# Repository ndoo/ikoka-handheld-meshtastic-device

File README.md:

# Ikoka Handheld Meshtastic Device

## Ikoka! (行こか!)

“行こか?” or “行こか!” is [Kansai dialect](https://en.wikipedia.org/wiki/Kansai_dialect) for “shall we go?” or “let’s go!”.

I hope that building these long-range Meshtastic designs inspires you to go on your next [DXing](https://en.wikipedia.org/wiki/DXing) adventure.

## Features

- LoRa
  - Up to 33 dBm (2 W) output power
  - 410–493 MHz (433 MHz band) or 850–930 MHz (868/915/923 MHz band)
- Bluetooth 5 LE
- Lithium-ion battery with charging
- 0.96" OLED display

Feature set above depends on part selection.

### Hardware

### Parts Selection

Several options are available depending on the feature set you need.

#### Microcontroller

- [Seeed Studio XIAO-nRF52840](https://www.seeedstudio.com/Seeed-XIAO-BLE-nRF52840-p-5201.html) - Bluetooth 5/LE

#### LoRa Module

- [E22-400M22S](https://www.cdebyte.com/products/E22-400M22S) (410–493 MHz at 22 dBm)
- [E22-400M30S](https://www.cdebyte.com/products/E22-400M30S) (410–493 MHz at 30 dBm)
- [E22-400M33S](https://www.cdebyte.com/products/E22-400M33S) (410–493 MHz at 33 dBm)
- [E22-900M22S](https://www.cdebyte.com/products/E22-900M22S) (850–930 MHz at 22 dBm)
- [E22-900M30S](https://www.cdebyte.com/products/E22-900M30S) (850–930 MHz at 30 dBm)
- [E22-900M33S](https://www.cdebyte.com/products/E22-900M33S) (850–930 MHz at 33 dBm)

#### Lithium-ion Battery (4.2V charging termination, optional)

- Lithium-polymer pouch battery cell (4.2V charge termination; connector: Molex PicoBlade 1x02P, pitch 1.25mm)

#### OLED Display (Optional)

- Generic SSD1306 0.96" OLED display modules with FPC connector ([Vishay OLED-128O064D-BPP3N00000](https://www.vishay.com/en/product/37902/) or generic OLEDs with the same connector dimensions and pinout)

## Firmware

### GPIO Assignment

| XIAO Pin | Function | XIAO-nRF52840 | XIAO-ESP32-S3 |
|---|---|---|---|
| 1 (D0) | User button | 2 (P0.02) | 1 |
| 2 (D1) | EBYTE E22 - DIO1 | 3 (P0.03) | 2 |
| 3 (D2) | EBYTE E22 - RST | 28 (P0.28) | 3 |
| 4 (D3) | EBYTE E22 - BUSY | 29 (P0.29) | 4 |
| 5 (D4) | EBYTE E22 - SPI NSS | 4 (P0.04) | 5 |
| 6 (D5) | EBYTE E22 - RXEN | 5 (P0.05) | 6 |
| 7 (D6) | SSD1306 OLED - I2C SDA | 43 (P1.11) | 43 |
| 8 (D7) | SSD1306 OLED - I2C SCL | 44 (P1.12) | 44 |
| 9 (D8) | EBYTE E22 - SPI SCK | 45 (P1.13) | 7 |
| 10 (D9) | EBYTE E22 - SPI MISO | 46 (P1.14) | 8 |
| 11 (D10) | EBYTE E22 - SPI MOSI | 47 (P1.15) | 9 |
| 12 | SSD1306 OLED - 3.3V | 3V3 | 3V3 |
| 13 | GND | GND | GND |
| 14 | NC | 5

#### XIAO-nRF52840

- EBYTE E22 LoRa
  - LoRa pins are identical to the officially-supported [Seeed Xiao NRF52840 Kit](https://www.seeedstudio.com/XIAO-nRF52840-Wio-SX1262-Kit-for-Meshtastic-p-6400.html) on [Meshtastic Web Flasher](https://flasher.meshtastic.org/)
  - LoRa will work out of the box on officially-supported firmware
  - Special consideration must be taken if using the E22-900M33S module
    - Set the transmit power to ≤ 9 dBm on first use (when setting the LoRa region)
    - **Transmit power must never be set greater than 9 dBm*- to avoid damaging the module's RF frontend
- SSD1306 OLED I2C
  - Pin D6/P1.11 and D7/P1.12 are [reserved for the L76K GPS module in the officially-supported variant](https://github.com/meshtastic/firmware/blob/152b8b1b0235bc461c6e4451fbcdac0987b8bf90/variants/seeed_xiao_nrf52840_kit/variant.h#L137-L138)
  - A custom firmware must be built to define these pins as I2C (TODO)
- User button
  - Pin D0/P0.02 is [reserved for the L76K GPS module in the officially supported variant](https://github.com/meshtastic/firmware/blob/152b8b1b0235bc461c6e4451fbcdac0987b8bf90/variants/seeed_xiao_nrf52840_kit/variant.h#L144)
  - A custom firmware must be built to define this pin as the user button (TODO)

## PCB Renders

### PCB Top

### PCB Bottom

### Rotating GIF

(Rendered with [kicad-render](https://github.com/linalinn/kicad-render).)

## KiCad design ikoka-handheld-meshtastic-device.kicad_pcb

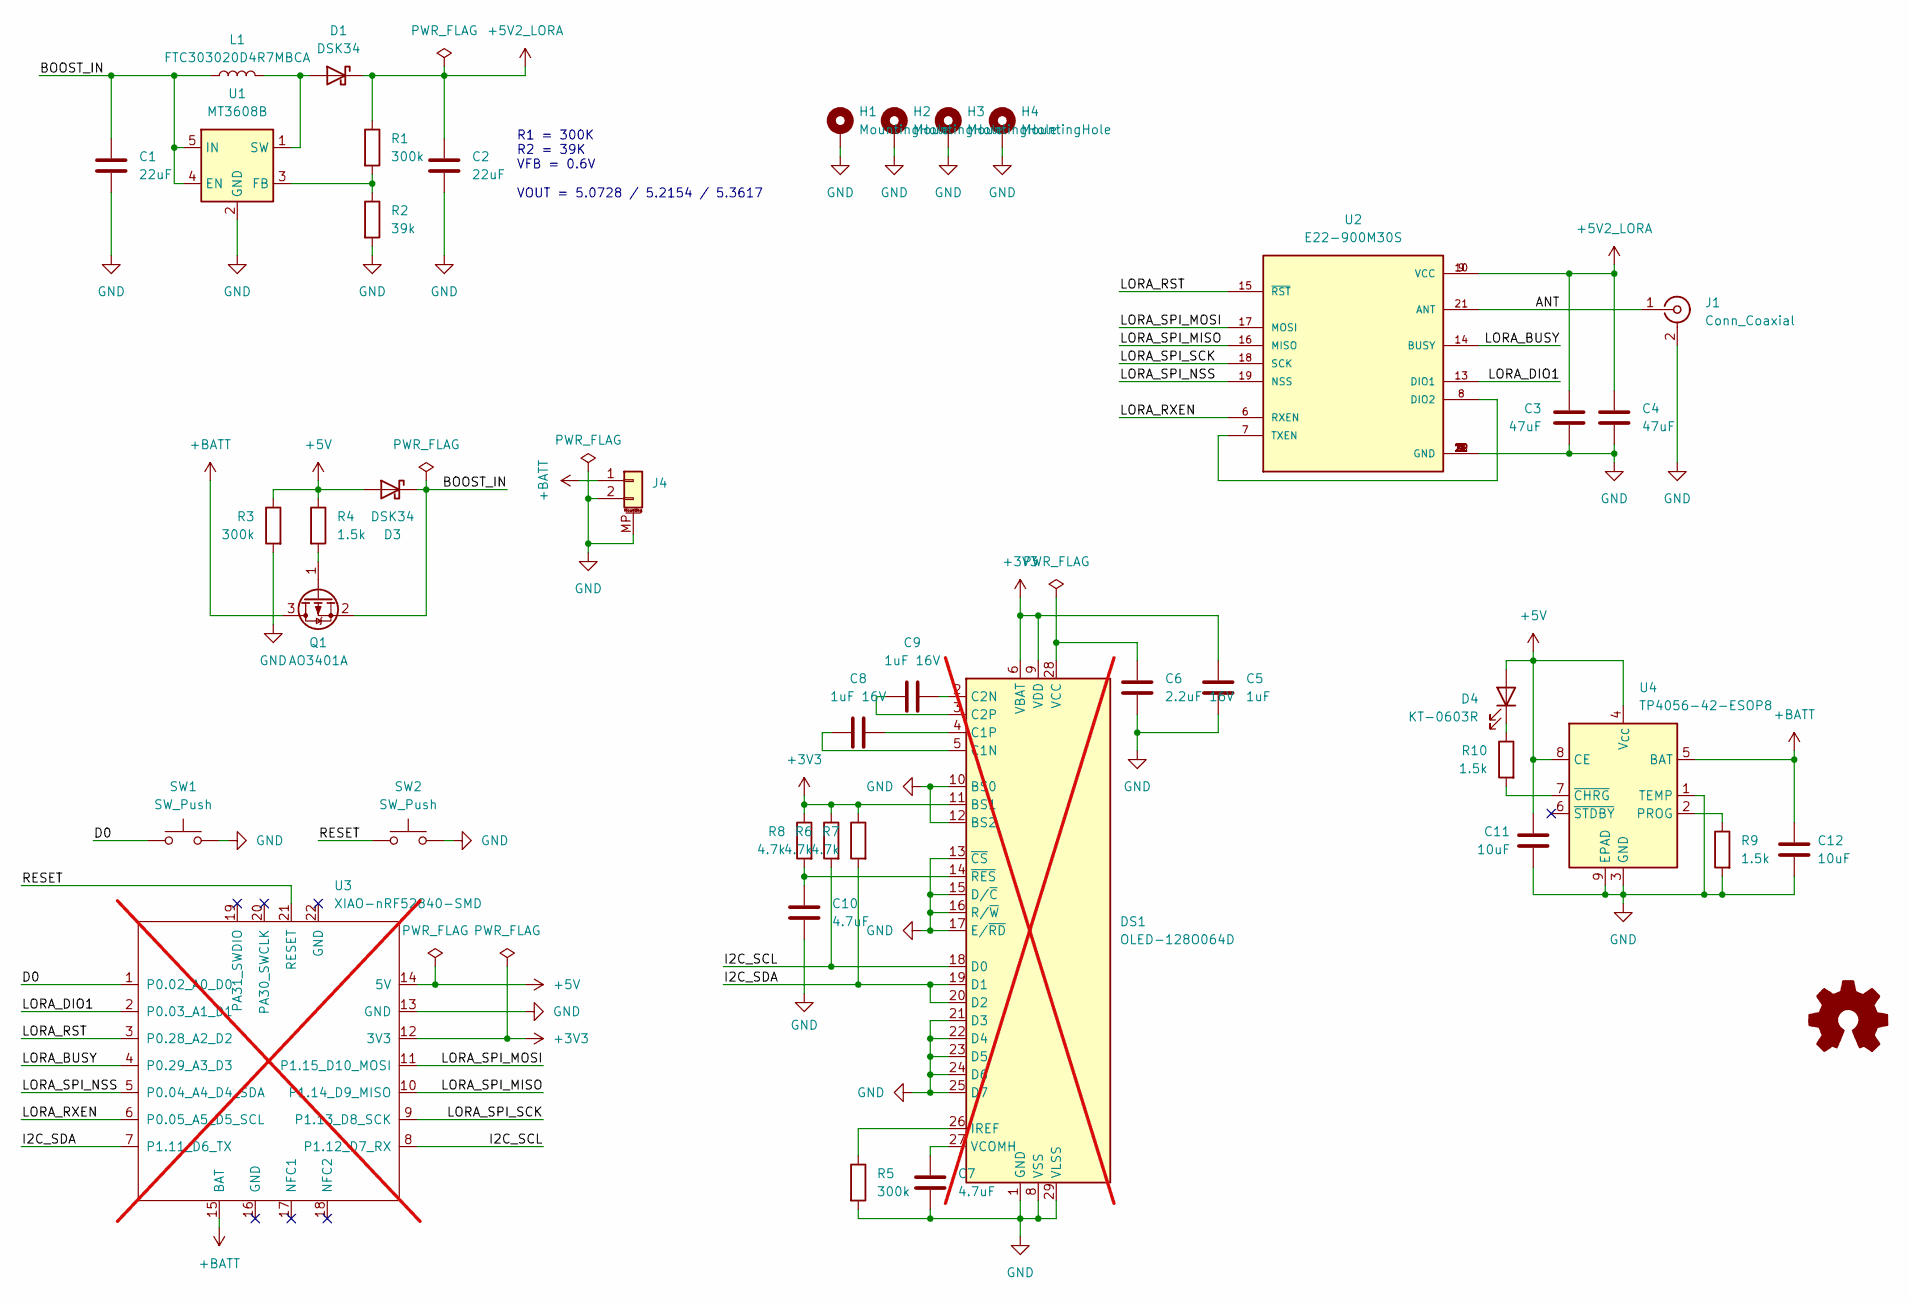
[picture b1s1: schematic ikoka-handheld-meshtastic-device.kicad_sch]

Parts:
C1, C2: 22uF; C_0603_1608Metric; LCSC C59461
C3, C4: 47uF; C_0805_2012Metric; LCSC C16780
C5: 1uF; C_0603_1608Metric; LCSC C15849
C6: 2.2uF 16V; C_0603_1608Metric; LCSC C23630
C7, C10: 4.7uF; C_0603_1608Metric; LCSC C19666
C8, C9: 1uF 16V; C_0603_1608Metric; LCSC C15849
C11, C12: 10uF; C_0603_1608Metric; LCSC C19702
D1, D3: DSK34; D_SOD-123F; LCSC C22466353
D4: KT-0603R; LED_0603_1608Metric; LCSC C2286
DS1: OLED-128O064D; not fitted
H1, H2, H3, H4: MountingHole; MountingHole_2.2mm_M2_Pad_Via
J1: Conn_Coaxial; SMA_Samtec_SMA-J-P-H-ST-EM1_EdgeMount; LCSC C5250058
J4: 1.25-2PWB; Molex_PicoBlade_53261-0271_1x02-1MP_P1.25mm_Horizontal; LCSC C2905009
L1: FTC303020D4R7MBCA; L_Changjiang_FTC303020D; LCSC C167747
Q1: AO3401A; SOT-23; LCSC C15127
R1, R3, R5: 300k; R_0603_1608Metric; LCSC C23024
R2: 39k; R_0603_1608Metric; LCSC C23153
R4, R9, R10: 1.5k; R_0603_1608Metric; LCSC C22843
R6, R7, R8: 4.7k; R_0603_1608Metric; LCSC C23162
SW1, SW2: SW_Push; TS-1088-AR02016; LCSC C720477
SYM1: Logo_Open_Hardware_Small; OSHW-Logo_7.5x8mm_SilkScreen
U1: MT3608B; SOT-23-6; LCSC C19189893
U2: E22-900M30S; XCVR_E22-900M30S; PARTREV 1.2; LCSC C411294
U3: XIAO-nRF52840-SMD; XIAO-nRF52840-SMD_Handsoldering; LCSC C9900124959; not fitted
U4: TP4056-42-ESOP8; SOIC-8-1EP_3.9x4.9mm_P1.27mm_EP2.41x3.3mm_ThermalVias; LCSC C16581

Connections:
+3V3: C5.1, DS1.6 (VBAT), DS1.9 (VDD), DS1.11 (BS1), R6.1, R7.1, R8.1, U3.12 (3V3)
+5V: C11.1, D3.2 (A), D4.2 (A), R3.1, R4.1, U3.14 (5V), U4.4 (V_{CC}), U4.8 (CE)
+5V2_LORA: C2.1, C3.1, C4.1, D1.1 (K), R1.1, U2.9 (VCC), U2.10 (VCC)
+BATT: C12.1, J4.1, Q1.3 (D), U3.15 (BAT), U4.5 (BAT)
/ANT: J1.1 (In), U2.21 (ANT)
/BOOST_IN: C1.1, D3.1 (K), L1.1, Q1.2 (S), U1.4 (EN), U1.5 (IN)
/D0: SW1.1, U3.1 (P0.02_A0_D0)
/I2C_SCL: DS1.18 (D0), R6.2, U3.8 (P1.12_D7_RX)
/I2C_SDA: DS1.19 (D1), DS1.20 (D2), R7.2, U3.7 (P1.11_D6_TX)
/LORA_BUSY: U2.14 (BUSY), U3.4 (P0.29_A3_D3)
/LORA_DIO1: U2.13 (DIO1), U3.2 (P0.03_A1_D1)
/LORA_RST: U2.15 (~RST), U3.3 (P0.28_A2_D2)
/LORA_RXEN: U2.6 (RXEN), U3.6 (P0.05_A5_D5_SCL)
/LORA_SPI_MISO: U2.16 (MISO), U3.10 (P1.14_D9_MISO)
/LORA_SPI_MOSI: U2.17 (MOSI), U3.11 (P1.15_D10_MOSI)
/LORA_SPI_NSS: U2.19 (NSS), U3.5 (P0.04_A4_D4_SDA)
/LORA_SPI_SCK: U2.18 (SCK), U3.9 (P1.13_D8_SCK)
/RESET: SW2.1, U3.21 (RESET)
GND: C1.2, C2.2, C3.2, C4.2, C5.2, C6.2, C7.2, C10.2, C11.2, C12.2, DS1.1 (GND), DS1.8 (VSS), DS1.10 (BS0), DS1.12 (BS2), DS1.13 (~CS), DS1.15 (D/~C), DS1.16 (R/~W), DS1.17 (E/~RD), DS1.21 (D3), DS1.22 (D4), DS1.23 (D5), DS1.24 (D6), DS1.25 (D7), DS1.29 (VLSS), DS1.30 (GND), H1.1, H2.1, H3.1, H4.1, J1.2 (Ext), J4.2, J4.MP (MountPin), R2.2, R3.2, R5.2, R9.2, SW1.2, SW2.2, U1.2 (GND), U2.1 (GND), U2.2 (GND), U2.3 (GND), U2.4 (GND), U2.5 (GND), U2.11 (GND), U2.12 (GND), U2.20 (GND), U2.22 (GND), U3.13 (GND), U4.1 (TEMP), U4.3 (GND), U4.9 (EPAD)
unnamed: D1.2 (A), L1.2, U1.1 (SW)
unnamed: D4.1 (K), R10.1
unnamed: C8.1, DS1.5 (C1N)
unnamed: C8.2, DS1.4 (C1P)
unnamed: C9.2, DS1.2 (C2N)
unnamed: C9.1, DS1.3 (C2P)
unnamed: DS1.26 (IREF), R5.1
unnamed: C6.1, DS1.28 (VCC)
unnamed: C7.1, DS1.27 (VCOMH)
unnamed: C10.1, DS1.14 (~RES), R8.2
unnamed: Q1.1 (G), R4.2
unnamed: R1.2, R2.1, U1.3 (FB)
unnamed: U2.7 (TXEN), U2.8 (DIO2)
unnamed: R9.1, U4.2 (PROG)
unnamed: R10.2, U4.7 (~CHRG)

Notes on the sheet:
R1 = 300K R2 = 39K VFB = 0.6V VOUT = 5.0728 / 5.2154 / 5.3617

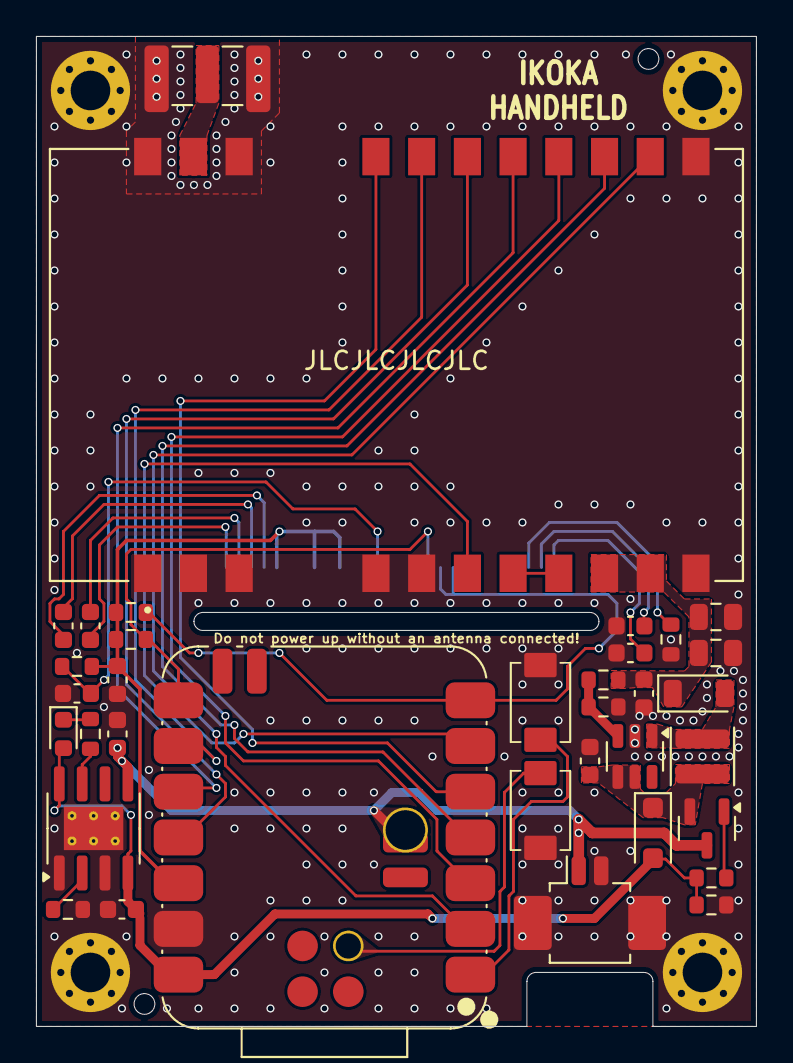
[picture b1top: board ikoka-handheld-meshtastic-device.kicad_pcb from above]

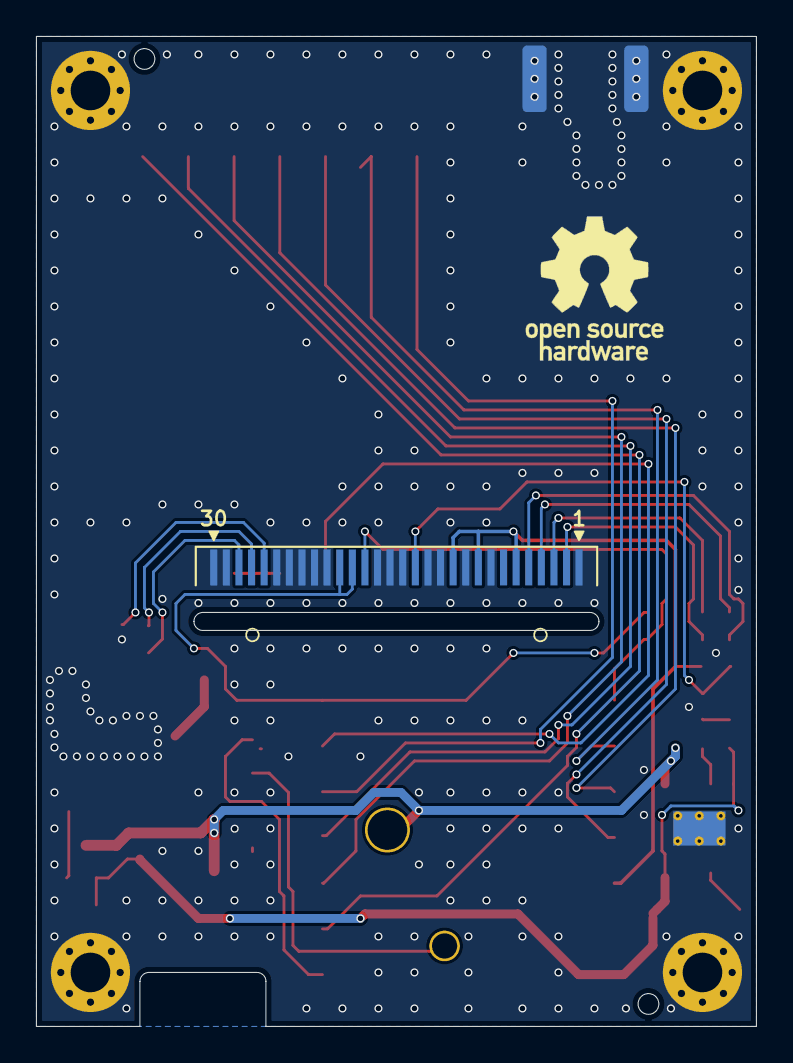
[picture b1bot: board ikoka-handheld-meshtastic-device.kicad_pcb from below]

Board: 2 copper layers, 40.0 x 55.0 mm, 41 parts (2 on the bottom side), 34 nets.

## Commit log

2025-06-29 BREAKING CHANGE: Redesign as Ikoka Handheld
2025-06-29 fix: Add BAT output capacitor on TP4056
2025-07-08 fix: Flip SSD1306 footprint (fixes #1)
2025-07-08 feat: Change TP4056 charge current from 1A to 780mA
    For a total of 880mA (780mA TP4056 + 100mA onboard XIAO charger).
    Most pouch cells the size of the PCB are around 1000mAh, and 1.1A charge rate is above 1C for these cells, which will increase battery wear.
2025-07-08 fix(pcbnew): Add user drawings for dimensions and fix hole alignment
2025-07-15 chore: Use fork of OPL_Kicad_Library with Handsoldering footprint
2025-07-15 fix: Change inductor from 22uH to 2.2uH, Move XIAO up 0.1mm
    - Change inductor from 22uH to 2.2uH
    - From: FTC303015D220MBCA
    - To: FNR3015S2R2MT
    - Lower DCR
    - Higher current headroom
    - Better transient response
2025-07-15 chore: Clear ERC and DRC errors/warnings
2025-07-15 fix(pcbnew): XIAO 3dmodel and footprint type again...
2025-07-15 feat(pcbnew): 3dmodel for TP4056
2025-07-15 chore: Update JLCPCB parts selection based on preceding changes
2025-07-15 feat(eeschema): Change MT3608 to MT3608B (newer part)
2025-07-15 chore(pcbnew): Move JLCJLCJLCJLC silk away from vias
2025-07-15 fix: OLED did not need to be mirrored, add pin 1 & 30 silk
2025-07-15 feat: Use more 1.5k and 300k resistors where possible to simplify BoM
2025-07-15 feat(pcbnew): Improve layout
    - All SX1262 traces to the back
    - Don't run SSD1306 charge pump and SX1262 traces on top of each other in parallel
    - Move SSD1306 reset circuit to bottom half of PCB
2025-07-15 feat: OSHW logo
2025-07-15 fix: MT3608B wrongly selected as MT3608L in JLCPCB DB
2025-07-15 fixup! fix: Change inductor from 22uH to 2.2uH, Move XIAO up 0.1mm
2025-07-21 Update XIAO nRF52840 footprint
2025-07-21 feat: Boost converter improvements
    - Change Schottky diode from DSK26 (Vf 0.7V, Iav 2A) to DSK34 (Vf 0.55V, Iav 3A)
    - Change inductor from FNR3015S2R2MT (2.2µH, 2A/2A, DCR 0.06Ω) to FTC303018D4R7MBCA (4.7µH, 4.2A/3A, DCR 0.087Ω)
2025-07-23 fix: Remove I2C 4.7kΩ pull-down resistors - The resistors are wrongly wired as pull-down to GND instead of pull-up to 3V3, I2C is open drain and requires pull-up - Remove them entirely and rely on nr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
    Fixes #3.
2025-07-24 fix: Add 4.7kΩ pull-up resistors on I2C bus (fixes #5)
